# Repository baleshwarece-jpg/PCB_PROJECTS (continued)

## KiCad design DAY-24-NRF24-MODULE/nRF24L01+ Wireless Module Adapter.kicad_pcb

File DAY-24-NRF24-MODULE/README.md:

# nRF24L01+ Wireless Module Adapter

**Day 24 / 30 — 30-Day PCB Design Challenge**

A breakout/adapter board that solves the single most common cause of nRF24L01+ instability: an undersized, noisy 3.3 V supply driving a radio with sharp current transients. Adds a dedicated LDO, bulk and local decoupling, and a 5V-tolerant level-shifted SPI interface so the module can be driven directly from a 5V microcontroller (Arduino Uno/Nano) without a separate logic-level converter board.

## Overview

The nRF24L01+ is a 2.4 GHz transceiver IC that operates from a 1.9–3.6 V supply and draws up to 11.3 mA in RX mode, but spikes to roughly 115 mA for short bursts during TX peak power output. Most low-cost breakout modules expose only VCC/GND/CE/CSN/SCK/MOSI/MISO/IRQ pins with no onboard regulation, relying entirely on the host board's 3.3 V rail. On an Arduino Uno, the onboard 3.3 V pin is sourced from the FTDI/USB regulator and is rated for only about 50 mA — far below the module's transient demand. The result is the classic symptom: the radio initializes, `radio.isChipConnected()` returns true, but `write()` calls silently fail or ACK payloads are dropped intermittently.

This board solves that at the hardware level: a dedicated AMS1117-3.3 LDO with adequate input headroom, a 10 µF tantalum bulk cap directly at the module's VCC pin (the fix most commonly cited for nRF24L01+ dropouts), and a 74LVC125A-based level shifter so SCK/MOSI/CSN/CE can be driven safely from 5 V logic without exceeding the nRF24L01+'s absolute maximum VIH.

## Specifications

| Parameter | Value |
|---|---|
| Input Voltage | 5V DC (from host MCU) or 3.3–6V via separate header |
| Regulated Output | 3.3V ±2%, AMS1117-3.3 |
| Max Module Current (TX peak) | 115 mA |
| Logic Input | 5V tolerant (level-shifted SPI + CE) |
| Logic Output (MISO, IRQ) | 3.3V native, passed through unshifted |
| SPI Clock | Up to 10 MHz (module rated 8 Mbps SPI per datasheet) |
| Module Connector | 2×4, 2.54 mm socket header (standard nRF24L01+ footprint) |
| Host Connector | 8-pin, 2.54 mm header (VCC, GND, CE, CSN, SCK, MOSI, MISO, IRQ) |
| Decoupling | 10 µF tantalum + 100 nF ceramic at module VCC, 1 µF at LDO output |
| PCB | 2-layer, 1 oz copper |

## Why an Adapter Board

Wiring an nRF24L01+ directly to a microcontroller is the default hobbyist approach and the most common source of "works sometimes" radio behavior:

**Supply transients:** The module's current draw during the PA ramp-up for TX is a fast edge, not a steady load. A long, thin jumper wire from a 3.3 V pin has enough series inductance and resistance that the voltage at the module sags below 1.9 V for microseconds — enough to reset the radio's internal state machine mid-packet. This is why the well-known fix in the hobbyist community is "add a capacitor across VCC and GND," but a loose electrolytic on a breadboard is itself a poor high-frequency decoupling solution; it needs to be paired with a low-ESR ceramic placed within a few millimeters of the pin.

**Logic level mismatch:** The nRF24L01+ datasheet lists an absolute maximum VIH of VDD + 0.3 V. At VDD = 3.3 V this is 3.6 V — below the 5 V logic level of an Arduino Uno's SPI pins. Many modules survive years of out-of-spec 5 V SPI signaling because the input is somewhat tolerant in practice, but it is out-of-spec operation and a documented cause of premature module failure and erratic behavior under temperature or supply variation. The 74LVC125A buffers SCK, MOSI, and CSN from 5 V down to a clean 3.3 V swing.

**Source impedance of the host 3.3V rail:** On boards like the Arduino Uno, the 3.3 V pin is not meant to supply more than ~50 mA continuously and has no bulk capacitance behind it on the host board itself. Running two or more nRF24L01+ modules from the same Uno 3.3 V pin (a common setup in multi-node projects) compounds this problem — a dedicated LDO on each adapter avoids contention entirely.

## Schematic Overview

**U1 — AMS1117-3.3 LDO Regulator**
Linear regulator, 1 A rated output, dropout voltage ~1.1 V at full load. Takes 5 V from the host and supplies a clean, locally-regulated 3.3 V rail dedicated to the radio module. Input decoupled with 1 µF ceramic, output decoupled with 10 µF tantalum directly at the regulator pin and a second 10 µF tantalum at the module VCC pin itself — two separate bulk caps to keep the high-frequency transient local to the load.

**U2 — 74LVC125A Quad Buffer**
Used as a one-directional level shifter for CE, CSN, SCK, and MOSI (4 channels, matching the 4 buffers on the package). Each buffer's OE pin tied to GND (always enabled, push-pull output). Inputs accept 5 V host logic; outputs swing rail-to-rail at the 3.3 V supply, which the nRF24L01+ datasheet specifies as the correct VIH/VIL reference.

**MISO and IRQ — unbuffered**
These are outputs from the module to the host. The nRF24L01+ output high level is referenced to its own 3.3 V VDD, and a 3.3 V high level is still recognized correctly by a 5 V host's VIH threshold (typically 0.6×VCC = 3.0 V on an Arduino Uno's ATmega328P). No level shifting needed in this direction, which also avoids adding propagation delay to the MISO line during SPI reads.

**C1 — 1 µF ceramic**
LDO input decoupling, placed within 5 mm of U1 VIN.

**C2 — 10 µF tantalum**
LDO output decoupling, placed at U1 VOUT.

**C3 — 10 µF tantalum**
Local bulk decoupling directly at the module's VCC socket pin — the single highest-impact component on this board for eliminating TX dropout failures. Placed within 3 mm of the 2×4 socket header VCC pin.

**C4 — 100 nF ceramic**
High-frequency decoupling in parallel with C3, same placement constraint.

**R1 — 10 kΩ pull-down on CE**
Holds CE low during power-up before the host MCU initializes the radio library, preventing the module from entering an undefined state with a floating CE pin.

**LED1 — Power indicator**
Green, 0603, 1 kΩ series resistor from the 3.3 V rail. Confirms the LDO is producing output independent of whether the host SPI bus is active.

## PCB Design Notes

- Designed in KiCad 8
- 1 oz copper, 2-layer — current levels are low (max ~150 mA), so this is a routing-density and decoupling-placement exercise rather than a power-handling one
- Ground pour on both layers, single-point stitched under U1 to minimize regulator switching noise coupling into the analog-sensitive RF module socket
- C3 and C4 placed on the same side and as close as physically possible to the module socket VCC pin — trace length here matters more than trace width at these current levels, since the goal is minimizing loop inductance, not resistive drop
- SPI traces (SCK, MOSI, MISO) length-matched within 2 mm and kept short to limit ringing at 10 MHz
- Module socket positioned at the board edge with the antenna trace/chip antenna of the nRF24L01+ module overhanging the PCB edge, keeping the ground pour and any metal at least 15 mm clear of the antenna per the module manufacturer's placement guidance
- Mounting holes: 2× M2.5, diagonal corners

## Getting Started

### Wiring

```
Host MCU (5V logic)        Adapter Board            nRF24L01+ Module
──────────────────────────────────────────────────────────────────
5V              ──────>    VCC (in)
GND             ──────>    GND
Digital Pin 9   ──────>    CE
Digital Pin 10  ──────>    CSN
Digital Pin 13  ──────>    SCK
Digital Pin 11  ──────>    MOSI
Digital Pin 12  <──────    MISO
                            VCC (out)    ──────>    VCC
                            GND          ──────>    GND
                            CE           ──────>    CE
                            CSN          ──────>    CSN
                            SCK          ──────>    SCK
                            MOSI         ──────>    MOSI
                            MISO         ──────>    MISO
                            IRQ          ──────>    IRQ (optional)
```

### Arduino Example (RF24 library)

```cpp
#include <SPI.h>
#include <RF24.h>

RF24 radio(9, 10);  // CE, CSN

const byte address[6] = "00001";

void setup() {
  Serial.begin(9600);
  radio.begin();
  radio.setPALevel(RF24_PA_LOW);   // start low, raise once link is verified
  radio.setDataRate(RF24_250KBPS);
  radio.openWritingPipe(address);
  radio.stopListening();
}

void loop() {
  const char text[] = "Hello";
  bool ok = radio.write(&text, sizeof(text));
  Serial.println(ok ? "Sent" : "Failed");
  delay(1000);
}
```

## BOM

| Reference | Part | Package | Value / Part No. |
|---|---|---|---|
| U1 | AMS1117-3.3 | SOT-223 | 3.3V LDO, 1A |
| U2 | 74LVC125A | TSSOP-14 | Quad buffer, 5V-tolerant input |
| C1 | Ceramic | 0603 | 1 µF / 16V |
| C2, C3 | Tantalum | Case A (1206) | 10 µF / 10V |
| C4 | Ceramic | 0402 | 100 nF / 16V |
| R1 | Resistor | 0402 | 10 kΩ |
| R2 | Resistor | 0402 | 1 kΩ (LED current limit) |
| LED1 | Green LED | 0603 | Power indicator |
| J1 | Pin header | 2.54 mm, 8-pin | Host connector |
| J2 | Socket header | 2.54 mm, 2×4 | nRF24L01+ module socket |

## Common Issues

**`radio.isChipConnected()` returns true but `write()` always fails**
Classic supply transient symptom. Confirm C3 is populated and soldered — this is the fix that resolves the large majority of reported nRF24L01+ reliability issues in the hobbyist community. Probe VCC at the module socket with a scope during a `write()` call; a healthy rail should not sag more than ~100 mV.

**Intermittent packets, works at close range only**
Lower `setPALevel()` to `RF24_PA_LOW` or `RF24_PA_MIN` first to rule out a marginal supply being unable to sustain `RF24_PA_HIGH` peak draw before assuming it's a range/antenna issue.

**Module gets warm**
The nRF24L01+ itself runs cool under normal operation. Warmth at the module usually indicates U1 is in dropout or a wiring short — check that host VIN is genuinely 5 V and not sagging under load from other peripherals sharing the same supply rail.

**SPI communication fails entirely (not just RF link)**
Verify U2's OE pins are tied low and check buffer pinout orientation — it is easy to swap an A/B (input/output) pair on the 74LVC125A given its symmetric pinout.

## Repository Structure

```
nRF24L01-Adapter/
├── hardware/
│   ├── nRF24_Adapter.kicad_pro
│   ├── nRF24_Adapter.kicad_sch
│   ├── nRF24_Adapter.kicad_pcb
│   ├── gerbers/
│   │   └── nRF24_Adapter_gerbers.zip
│   └── bom/
│       └── nRF24_Adapter_BOM.csv
├── docs/
│   ├── schematic.pdf
│   ├── nRF24L01_Datasheet.pdf
│   └── assembly_notes.md
└── README.md
```

## 30-Day PCB Challenge Progress

| Day | Board | Status |
|---|---|---|
| 22 | (previous board) | Complete |
| 23 | (previous board) | Complete |
| 24 | nRF24L01+ Wireless Module Adapter | Complete |
| 25 | Coming soon | — |

## License

Hardware design files released under CERN OHL v2 — Permissive.

## References

- nRF24L01+ Datasheet — Nordic Semiconductor
- AMS1117 Datasheet — Advanced Monolithic Systems
- 74LVC125A Datasheet — Texas Instruments
- RF24 Library — nRF24/RF24 (GitHub)
- KiCad EDA

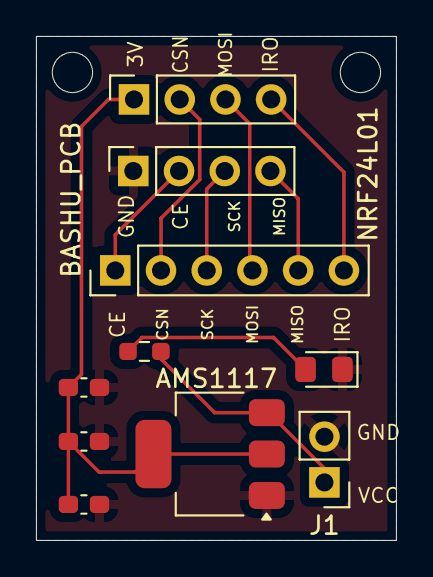
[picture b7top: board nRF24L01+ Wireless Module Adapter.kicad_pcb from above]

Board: 2 copper layers, 20.0 x 28.0 mm, 10 parts (0 on the bottom side), 10 nets.

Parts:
AMS1117: AMS1117-3.3; SOT-223-3_TabPin2
C1, C2, C3: C; C_0603_1608Metric_Pad1.08x0.95mm_HandSolder
D1: LED; LED_0805_2012Metric_Pad1.15x1.40mm_HandSolder
GND: Conn_01x04_Pin; PinSocket_1x04_P2.54mm_Vertical
J1: Conn_01x02_Pin; PinHeader_1x02_P2.54mm_Vertical
J3: Conn_01x04_Pin; PinSocket_1x04_P2.54mm_Vertical
J4: Conn_01x06_Pin; PinHeader_1x06_P2.54mm_Vertical
R1: R; R_0603_1608Metric_Pad0.98x0.95mm_HandSolder

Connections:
/3v: AMS1117.2 (VO), C1.1, C2.1, C3.1, J3.1
/5v: AMS1117.3 (VI), J1.1, R1.1
/CE: GND.2, J4.1
/CSN: J3.2, J4.2
/IRO: J3.4, J4.6
/MISO: GND.4, J4.5
/MOSI: J3.3, J4.4
/SCK: GND.3, J4.3
GND: AMS1117.1 (GND), C1.2, C2.2, C3.2, D1.1 (K), GND.1, J1.2
unnamed: D1.2 (A), R1.2

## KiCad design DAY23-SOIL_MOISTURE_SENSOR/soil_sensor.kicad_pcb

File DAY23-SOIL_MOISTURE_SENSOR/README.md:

# Resistive Soil Moisture Sensor Module
**Day 23 / 30 — 30-Day PCB Design Challenge**

A resistive soil moisture sensor module with a comparator-based digital threshold output and a buffered analog output, designed for irrigation control, plant monitoring, and low-power garden automation. Includes corrosion-mitigation measures absent from most low-cost commercial versions of this sensor type.

---

## Overview

Resistive soil moisture sensing works by measuring the conductivity between two exposed electrodes inserted into soil — wetter soil contains more dissolved ions and conducts better, lowering the measured resistance between the probes. This is the simplest and lowest-cost moisture sensing method available, but it has a well-known durability problem: applying a continuous DC voltage across two exposed metal electrodes in damp soil drives electrolytic corrosion, visibly degrading bare copper or even ENIG-finished probes within weeks of continuous operation.

This board addresses that directly by gating power to the probes rather than leaving them continuously energized, and by routing the sensing signal through a comparator stage for a clean digital threshold output in addition to the raw analog reading. The result is a sensor intended to actually survive extended outdoor or potted-plant deployment rather than one optimized only for bench demonstration.

---

## Specifications

| Parameter | Value |
|---|---|
| Supply Voltage | 3.3V – 5V |
| Sensing Method | Resistive (two-electrode conductivity) |
| Analog Output | 0 – VCC, proportional to soil moisture |
| Digital Output | Threshold comparator, open-drain, adjustable via onboard potentiometer |
| Probe Drive | Switched (not continuous) — gated by onboard transistor |
| Probe Spacing | 20 mm center-to-center |
| Probe Finish | ENIG (gold) — corrosion-resistant, not bare copper |
| Quiescent Current | <1 µA between sensing pulses (probe drive off) |
| PCB | 2-layer, 1 oz copper |

---

## Why Switched Probe Drive

Most low-cost soil moisture boards on the market wire the probes directly across the supply rail with no switching at all. This works as a demonstration but is a poor long-term design choice: continuous DC current through soil between two dissimilar or even identical metal electrodes drives galvanic and electrolytic corrosion, depositing metal ions from one electrode and accelerating pitting and material loss. Within several weeks of continuous outdoor operation, bare copper probes visibly oxidize and the sensor's readings drift as the electrode surface area and composition change.

This board instead gates the probe supply through Q1, energizing the probes only for the brief window needed to take a reading and leaving them unpowered the rest of the time. Combined with an ENIG (gold) finish on the probe pads rather than bare copper, this substantially reduces the corrosion rate, since gold is far less reactive than copper and the probes are not under continuous bias even when they are connected to soil moisture.

---

## Signal Path

```
Microcontroller GPIO (probe enable)
        |
        v
   Q1 (P-channel MOSFET, probe supply switch)
        |
        v
   Probe pair in soil (variable resistance)
        |
        v
   R1 (fixed reference resistor, forms divider with soil resistance)
        |
        v
   Analog node — voltage proportional to soil conductivity
        |
        +----------------------+
        |                      |
        v                      v
  Buffered analog out     Comparator (U1)
   (to ADC)                    |
                                v
                         Digital threshold out
                         (to GPIO interrupt/digital read)
```

The probe pair and R1 form a voltage divider. Dry soil presents high resistance, so the divider output sits close to VCC; wet soil presents lower resistance, pulling the divider output down. This is the inverse of what some datasheets describe depending on which leg of the divider the probes occupy — this board places the probes on the high side, so the analog output decreases as soil moisture increases. Firmware or downstream processing should account for this polarity.

---

## Schematic Overview

**Q1 — P-channel MOSFET (probe supply switch)**
Gate driven by a microcontroller GPIO through R2. When the GPIO pulls the gate low, Q1 conducts, applying VCC to the probe pair for the duration of the read. When the GPIO is released (high or floating with R3 pull-up), Q1 turns off and the probes are unpowered, eliminating standing DC bias across the electrodes between readings.

**R1 — Reference Resistor (10 kOhm)**
Forms a voltage divider with the soil resistance between the probes. Value selected to center the expected sensing range within typical potted-soil and garden-soil resistance values, which commonly fall in the range of several kOhm (saturated) to several hundred kOhm (dry) depending on soil composition and electrode spacing.

**U1 — Comparator (LM393 or equivalent)**
Compares the analog sensing node against a reference voltage set by RV1. Output is open-drain, pulled up through R5 to VCC, producing a clean digital HIGH/LOW threshold signal suitable for a GPIO interrupt-driven "soil is dry" alert without requiring the microcontroller to poll an ADC continuously.

**RV1 — Threshold Potentiometer (10 kOhm trimmer)**
Sets the comparator's switching threshold, allowing the digital "dry" trigger point to be calibrated for different soil types and probe conditions rather than fixed at a single factory value.

**U2 — Buffer / Voltage Follower (second channel of LM393-class comparator IC, or dedicated op-amp)**
Buffers the analog sensing node before it reaches the output header, preventing the downstream ADC's input impedance or any cable capacitance from loading the relatively high-impedance soil sensing divider and distorting the reading.

**R2 — Gate Resistor (1 kOhm)**
Limits gate drive current to Q1 and damps switching transients.

**R3 — Gate Pull-up (10 kOhm)**
Holds Q1's gate high (off state) if the control GPIO is left floating or set to a high-impedance input during microcontroller reset or sleep, ensuring the probes default to unpowered rather than energized.

**R4 — Analog Output Pull-down (100 kOhm)**
Defines a known idle state on the analog output node when the probe drive is off, preventing a floating reading between sensing pulses.

**C1 — Supply Decoupling (100 nF)**
At the comparator IC's VCC pin.

**C2 — Sensing Node Filter (10 nF)**
Across the analog sensing node to GND, providing basic noise filtering against the relatively high source impedance of the soil divider, which is otherwise susceptible to picking up switching noise or RF interference.

---

## PCB Design Notes

- Designed in **KiCad 8**
- Probe pads finished in ENIG rather than bare HASL/copper — gold finish substantially reduces oxidation rate when the probes are intermittently biased in damp soil
- Probe pads sized generously (3 mm width, 20 mm spacing) to maximize sensing area and reduce sensitivity to minor soil contact variation
- No solder mask over the probe pads themselves — exposed plated copper/gold is the sensing surface
- Probe traces routed with adequate clearance from each other along their length to avoid any unintended leakage path other than through the soil itself
- Comparator and buffer circuitry placed away from the probe area, physically separated to reduce the chance of moisture or condensation affecting the active components if the board is mounted in a humid environment
- Optional conformal coating area defined around the active circuitry (excluding probe pads) for builds intended for sustained outdoor exposure
- Mounting hole provided above the probe section for zip-tie or bracket mounting at a fixed soil depth

---

## Getting Started

### Pinout

| Pin | Signal | Description |
|---|---|---|
| VCC | Supply | 3.3V – 5V |
| GND | Ground | Common ground |
| EN | Probe enable | Active-low GPIO input, gates probe power |
| AOUT | Analog output | Buffered, proportional to soil conductivity |
| DOUT | Digital output | Open-drain threshold comparator output |

### Arduino Example — Gated Reading

```cpp
#define EN_PIN    7
#define AOUT_PIN  A0
#define DOUT_PIN  2

void setup() {
  pinMode(EN_PIN, OUTPUT);
  digitalWrite(EN_PIN, HIGH); // probes off by default
  pinMode(DOUT_PIN, INPUT_PULLUP);
  Serial.begin(115200);
}

int readMoisture() {
  digitalWrite(EN_PIN, LOW);   // energize probes
  delay(10);                   // allow reading to settle
  int raw = analogRead(AOUT_PIN);
  digitalWrite(EN_PIN, HIGH);  // de-energize probes
  return raw;
}

void loop() {
  int reading = readMoisture();
  // Lower raw value = wetter soil (probes on high side of divider)
  int moisturePercent = map(reading, 1023, 300, 0, 100);
  moisturePercent = constrain(moisturePercent, 0, 100);

  Serial.print("Raw: ");
  Serial.print(reading);
  Serial.print("  Moisture: ");
  Serial.print(moisturePercent);
  Serial.println("%");

  delay(60000); // read once per minute — no need for continuous sensing
}
```

### Calibration

Raw ADC values at full dry and full wet conditions vary with probe spacing, soil composition, and supply voltage, and should be measured for the specific deployment rather than assumed:

1. With probes in completely dry soil (or air), record the raw ADC reading — this is the dry endpoint.
2. With probes fully inserted in saturated, freshly watered soil, record the raw ADC reading — this is the wet endpoint.
3. Use these two values in place of the placeholder `1023, 300` range in the `map()` call above.

### Threshold (Digital Output) Calibration

Adjust RV1 while monitoring DOUT and observing soil at the desired trigger moisture level — turn the trimmer until DOUT transitions state at that point. This sets the "irrigation needed" threshold in hardware, independent of any microcontroller calibration.

---

## BOM

| Reference | Part | Package | Value / Part No. |
|---|---|---|---|
| Q1 | P-channel MOSFET | SOT-23 | AO3401 or equivalent |
| U1, U2 | LM393 (dual comparator) | SOIC-8 | Comparator + buffer |
| RV1 | Trimmer potentiometer | 3 mm SMD | 10 kOhm |
| R1 | Resistor | 0402 | 10 kOhm (sense reference) |
| R2 | Resistor | 0402 | 1 kOhm (gate) |
| R3 | Resistor | 0402 | 10 kOhm (gate pull-up) |
| R4 | Resistor | 0402 | 100 kOhm (output pull-down) |
| R5 | Resistor | 0402 | 10 kOhm (comparator output pull-up) |
| C1 | Ceramic | 0402 | 100 nF |
| C2 | Ceramic | 0402 | 10 nF |
| J1 | Pin header | 2.54 mm, 5-pin | VCC / GND / EN / AOUT / DOUT |
| — | Probe pads | PCB (ENIG finish) | Exposed copper, no mask |

---

## Common Issues

**Readings drift over weeks of deployment**
Some corrosion is still expected over long timescales even with switched drive and ENIG finish, since this is a fundamental limitation of resistive sensing rather than something fully solved by these mitigations. Periodic recalibration of the dry/wet endpoints is recommended for installations expected to run for months. For permanent, maintenance-free deployments, a capacitive soil moisture sensor avoids electrode corrosion entirely, at higher cost and circuit complexity.

**Reading stuck at dry value regardless of actual soil moisture**
Verify Q1 is actually switching — probe the drain side of Q1 during a read cycle to confirm voltage is present at the probes only when EN is asserted. Check that the probe pads have good physical contact with soil and are not coated in residue or mineral buildup.

**Digital output never triggers, or triggers immediately at any moisture level**
RV1 threshold is set outside the range produced by the analog sensing circuit. Re-calibrate RV1 while monitoring the analog output to find the correct trimmer position for the desired trigger point.

**Noisy or unstable analog readings**
Confirm C2 is populated at the sensing node. Increase the settling delay between asserting EN and sampling AOUT if the probe supply rail or sensing node has not fully stabilized — 10 ms is typically sufficient but very long probe wiring runs may require more.

**Probes show visible corrosion despite switched drive**
Confirm firmware is not leaving EN asserted continuously (defeating the switching mitigation entirely) and check the actual duty cycle of probe energization against the intended sensing interval.

## Repository Structure

```
Soil-Moisture-Sensor/
├── hardware/
│   ├── Soil_Moisture.kicad_pro
│   ├── Soil_Moisture.kicad_sch
│   ├── Soil_Moisture.kicad_pcb
│   ├── gerbers/
│   │   └── Soil_Moisture_gerbers.zip
│   └── bom/
│       └── Soil_Moisture_BOM.csv
├── docs/
│   ├── schematic.pdf
│   ├── LM393_Datasheet.pdf
│   └── assembly_notes.md
└── README.md
```

---

## 30-Day PCB Challenge Progress

| Day | Board | Status |
|---|---|---|
| 21 | Low-Power Microphone Preamplifier (MAX4468) | Complete |
| 22 | MCP2551 CAN Bus Transceiver Breakout | Complete |
| **23** | **Resistive Soil Moisture Sensor Module** | **Complete** |
| 24 | Coming soon | — |

---

## License

Hardware design files released under **CERN OHL v2 — Permissive**.

---

## References

- [LM393 Datasheet — Texas Instruments](https://www.ti.com/lit/ds/symlink/lm393.pdf)
- [AO3401 Datasheet — Alpha & Omega Semiconductor](https://www.aosmd.com/res/datasheets/AO3401.pdf)
- [KiCad EDA](https://www.kicad.org/)

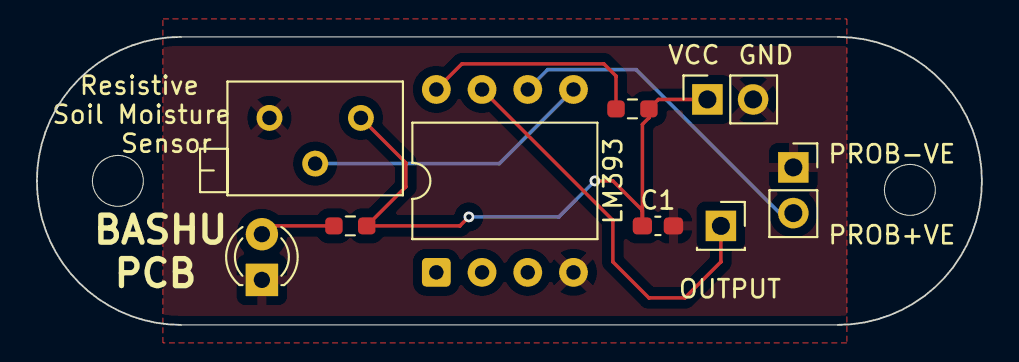
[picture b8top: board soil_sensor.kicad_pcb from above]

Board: 2 copper layers, 52.5 x 16.0 mm, 9 parts (0 on the bottom side), 7 nets.

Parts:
C1: C; C_0603_1608Metric_Pad1.08x0.95mm_HandSolder
D1: LED; LED_D3.0mm
INPUT: Conn_01x02_Pin; PinSocket_1x02_P2.54mm_Vertical
J2: Conn_01x02_Pin; PinSocket_1x02_P2.54mm_Vertical
LM393: LM393; DIP-8_W10.16mm
OUTPUT: Conn_01x01_Pin; PinSocket_1x01_P2.54mm_Vertical
R1, R2: R; R_0603_1608Metric_Pad0.98x0.95mm_HandSolder
RV1: R_Potentiometer; Potentiometer_Bourns_3299Z_Horizontal

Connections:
GND: C1.2, D1.1 (K), INPUT.1, J2.2, LM393.4 (V-), RV1.3
unnamed: D1.2 (A), R2.2
unnamed: INPUT.2, LM393.6 (-)
unnamed: LM393.7, OUTPUT.1
unnamed: LM393.5 (+), RV1.2
unnamed: LM393.8 (V+), R1.1
VCC: C1.1, J2.1, R1.2, R2.1, RV1.1

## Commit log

2026-05-03 Create README for AC to DC Regulator project
    Added README with project overview and components.
2026-05-03 Add image reference to README
2026-05-03 Update README with image previews
2026-05-03 Update PCB image link in README
2026-05-03 Fix circuit image link in README
    Updated image link for circuit preview in README.
2026-05-03 Enhance README with project details and goals
    Added progress and goal sections to the README.
2026-05-04 Create DAY2 TRANSFORMERLESS POWER SUPPLY
2026-05-04 Add README for Transformerless Power Supply project
    Added detailed README for the Transformerless Power Supply project, including overview, components, functionalities, working principle, design considerations, applications, safety notes, future impro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
2026-05-04 Add visuals to README for transformerless power supply
    Added project visuals including schematic, PCB layout, and 3D view.
2026-05-05 Add README for Servo Tester PCB design project
    This README provides an overview of the Servo Tester PCB design project, detailing components, working principles, functionalities, design highlights, applications, future enhancements, and a project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
2026-05-06 Add README for Motor Speed Control Circuit project
    This README outlines the Motor Speed Control Circuit project, detailing components, functionalities, applications, and future improvements.
2026-05-06 Update image links in README.md for visuals
2026-05-14 Create README for LM386 Audio Amplifier PCB project
    Added README.md for LM386 Audio Amplifier project, detailing components, functionalities, and design process.
2026-05-14 Update README with project images
    Added schematic, PCB layout, and 3D view images to the README.
2026-05-14 Rename DAY 5 LM389/README.md to DAY 5 LM389/DAY-5-LM386-AUDIO-AMPLIFIER/README.md
2026-05-14 Add README for LM386 Audio Amplifier project
    Added detailed README for LM386 Audio Amplifier project, including project overview, components used, functionalities, project description, images, applications, and future enhancements.
2026-05-16 Add README for USB 5V Regulated Power Supply PCB
    Added detailed project documentation for USB 5V regulated power supply PCB, including components, working principle, features, applications, and learning outcomes.
2026-05-16 Add project preview images to README
    Added additional project preview images to the README.
2026-05-17 Add README for 3.3V LDO Voltage Regulator Board
    This README provides an overview of a 3.3V LDO Voltage Regulator board designed in KiCad, including specifications, features, schematic images, KiCad setup instructions, and design notes.
2026-05-17 Revise README for clarity and project details
    Updated README to enhance project descriptions and structure.
2026-05-17 Refactor README for improved organization and detail
    Updated README to enhance structure and clarity, including project descriptions and goals.
2026-05-26 Create Pushbutton LED Controller design in KiCad
    Designed a Pushbutton LED Controller using KiCad, addressing challenges like switch bouncing and floating inputs. This project emphasizes the importance of pull-up resistors, transistor switching, an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
2026-05-29 Add README for Arduino Nano Extension Board project
    This README provides an overview of the Arduino Nano Extension Board project, detailing its objectives, features, design considerations, and applications.
2026-05-29 Enhance README with project details and instructions
    Expanded the README to include detailed project overview, features, design considerations, and getting started instructions for the Arduino Nano Extension Board.
2026-06-05 Update README.md to remove structure and add license
    Removed repository structure section and added license information.
2026-06-05 Create README.md for DHT11 sensor interface project
    Added detailed documentation for the DHT11 Temperature & Humidity Sensor Interface, including project overview, specifications, design notes, and getting started instructions.
2026-06-05 Add README for IR Remote Receiver Module
    Added detailed documentation for the IR Remote Receiver Module, including its functionality, specifications, and usage instructions.
2026-06-18 Add README for Piezo Buzzer Breakout Board project
    Added detailed README for Piezo Buzzer Breakout Board project, including project overview, working principle, schematic components, bill of materials, design notes, and repository structure.
2026-06-18 Add README for LDR Sensor Module
    Added detailed documentation for the LDR sensor module, including project overview, working principle, schematic components, bill of materials, pin header descriptions, LDR characteristics, design no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
2026-06-18 Add README for 4-Level Battery Indicator project
    Added README.md for Day 16 project detailing the 4-Level Battery Indicator module, including project overview, working principle, schematic components, bill of materials, and design notes.
2026-06-19 Rename README.md to reflect DAY19 changes
2026-06-19 Create README.md for motor driver project
    Add detailed README for Discrete MOSFET H-Bridge Motor Driver
2026-06-19 Add README for MCP2551 CAN Bus Transceiver Breakout
    Added detailed README for MCP2551 CAN Bus Transceiver Breakout, including specifications, wiring instructions, and common issues.
2026-06-20 Create README for LM2596 Adjustable Buck Converter
    Added detailed documentation for the LM2596 Adjustable Buck Converter, including specifications, layout considerations, and common issues.
2026-06-20 Add additional screenshot to README.md
2026-06-20 Add README for MPU6050 IMU breakout board
    Added detailed README for MPU6050 IMU breakout board, including specifications, wiring instructions, examples, and common issues.
2026-06-20 Create README for PAM8403 Class-D Stereo Amplifier
    Added detailed README for PAM8403 Class-D Stereo Amplifier, including specifications, layout considerations, and usage instructions.
2026-06-20 Revise README for 30-Day PCB Design Challenge
    Updated the README to reflect a 30-Day PCB Design Challenge format, including project goals, repository structure, and progress.
